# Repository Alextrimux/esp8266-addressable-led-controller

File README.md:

# esp8266-addressable-led-controller
The small hardware project of the addressable led controller on esp8266.

It is designed especially for using [WLED firmware](https://github.com/Aircoookie/WLED).

Features:
 - two-channel output for LED strip
 - reverse polarity protection
 - plug-in fuse
 - additional pins for extension

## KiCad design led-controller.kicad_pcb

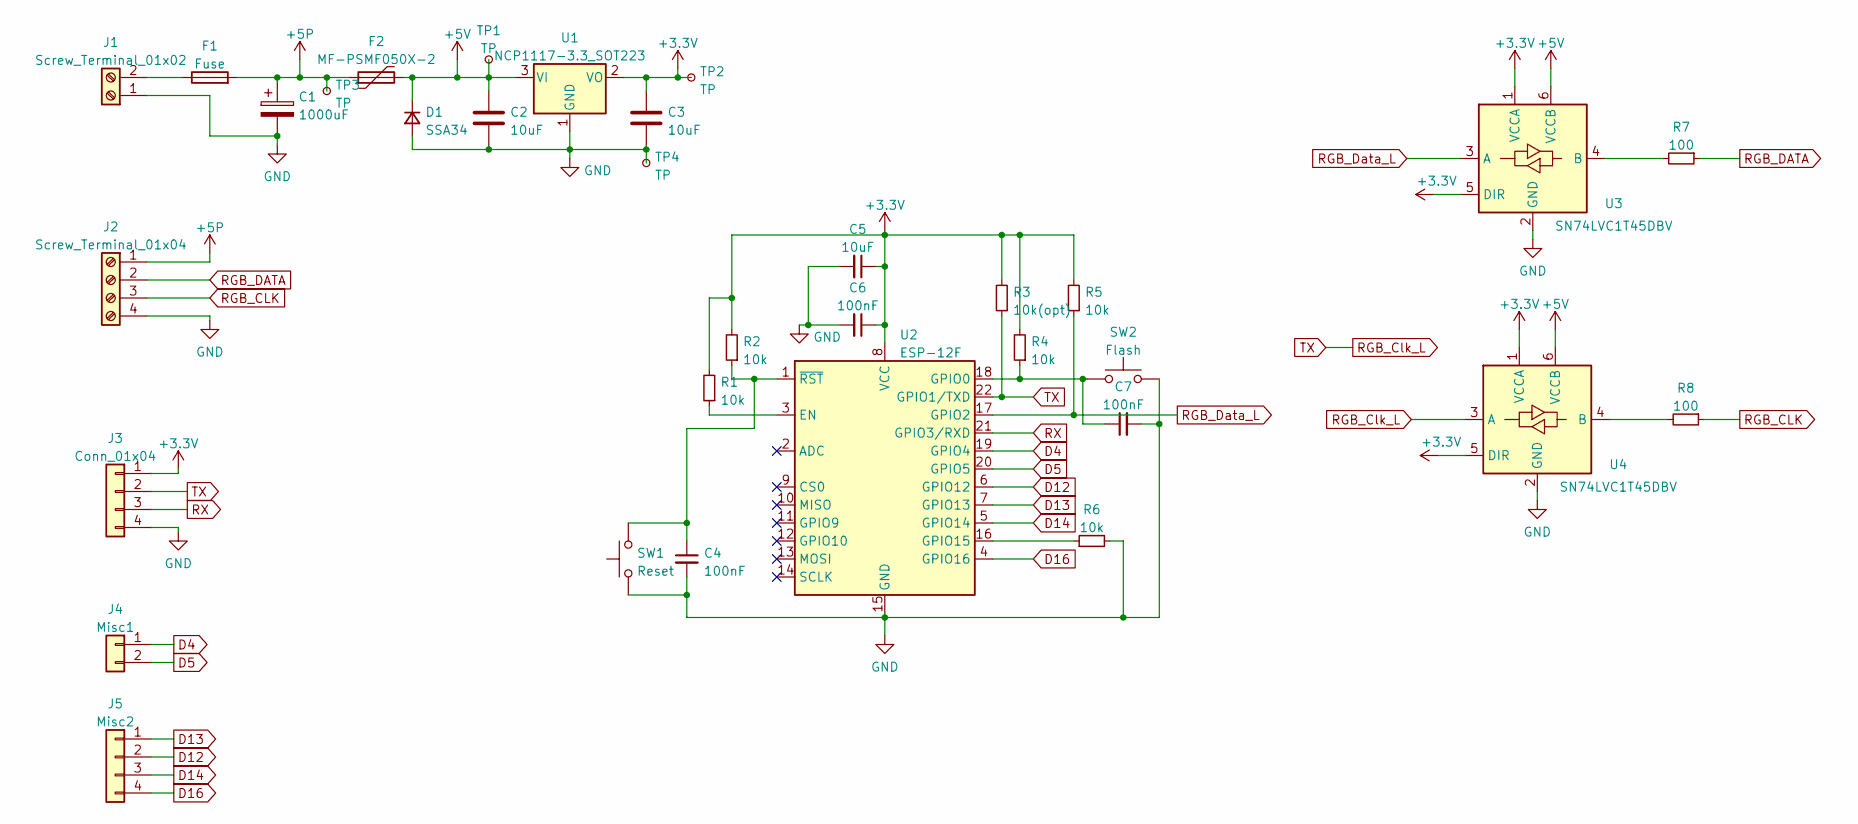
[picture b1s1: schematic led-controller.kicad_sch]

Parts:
C1: 1000uF; CP_Radial_D8.0mm_P3.50mm
C2, C3, C5: 10uF; C_0603_1608Metric_Pad1.08x0.95mm_HandSolder
C4, C6, C7: 100nF; C_0603_1608Metric_Pad1.08x0.95mm_HandSolder
D1: SSA34; D_SMA
F1: Fuse; XF-505P
F2: MF-PSMF050X-2; Fuse_0805_2012Metric_Pad1.15x1.40mm_HandSolder
J1: Screw_Terminal_01x02; TerminalBlock_bornier-2_P5.08mm
J2: Screw_Terminal_01x04; TerminalBlock_bornier-4_P5.08mm
J3: Conn_01x04; PinHeader_1x04_P2.54mm_Vertical
J4: Misc1; PinHeader_1x02_P2.54mm_Vertical
J5: Misc2; PinHeader_1x04_P2.54mm_Vertical
R1, R2, R4, R5, R6: 10k; R_0603_1608Metric_Pad0.98x0.95mm_HandSolder
R3: 10k(opt); R_0603_1608Metric_Pad0.98x0.95mm_HandSolder
R7, R8: 100; R_0603_1608Metric_Pad0.98x0.95mm_HandSolder
SW1: Reset; SW_SPST_TL3342
SW2: Flash; SW_SPST_TL3342
TP1, TP2, TP3, TP4: TP; TestPoint_Pad_D1.5mm
U1: NCP1117-3.3_SOT223; SOT-223-3_TabPin2
U2: ESP-12F; ESP-12E
U3, U4: SN74LVC1T45DBV; SOT-23-6

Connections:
+3V3: C3.1, C5.1, C6.1, J3.1, R1.2, R2.2, R3.2, R4.2, R5.2, TP2.1, U1.2 (VO), U2.8 (VCC), U3.1 (VCCA), U3.5 (DIR), U4.1 (VCCA), U4.5 (DIR)
+5P: C1.1, F1.2, F2.1, J2.1, TP3.1
+5V: C2.1, D1.1 (K), F2.2, TP1.1, U1.3 (VI), U3.6 (VCCB), U4.6 (VCCB)
D4: J4.1, U2.19 (GPIO4)
D5: J4.2, U2.20 (GPIO5)
D12: J5.2, U2.6 (GPIO12)
D13: J5.1, U2.7 (GPIO13)
D14: J5.3, U2.5 (GPIO14)
D16: J5.4, U2.4 (GPIO16)
GND: C1.2, C2.2, C3.2, C4.2, C5.2, C6.2, C7.2, D1.2 (A), J1.1, J2.4, J3.4, R6.2, SW1.1, SW2.2, TP4.1, U1.1 (GND), U2.15 (GND), U3.2 (GND), U4.2 (GND)
unnamed: C4.1, R2.1, SW1.2, U2.1 (~RST)
unnamed: C7.1, R4.1, SW2.1, U2.18 (GPIO0)
unnamed: F1.1, J1.2
unnamed: R1.1, U2.3 (EN)
unnamed: R6.1, U2.16 (GPIO15)
unnamed: R7.2, U3.4 (B)
unnamed: R8.2, U4.4 (B)
RGB_CLK: J2.3, R8.1
RGB_Clk_L: J3.2, R3.1, U2.22 (GPIO1/TXD), U4.3 (A)
RGB_DATA: J2.2, R7.1
RGB_Data_L: R5.1, U2.17 (GPIO2), U3.3 (A)
RX: J3.3, U2.21 (GPIO3/RXD)

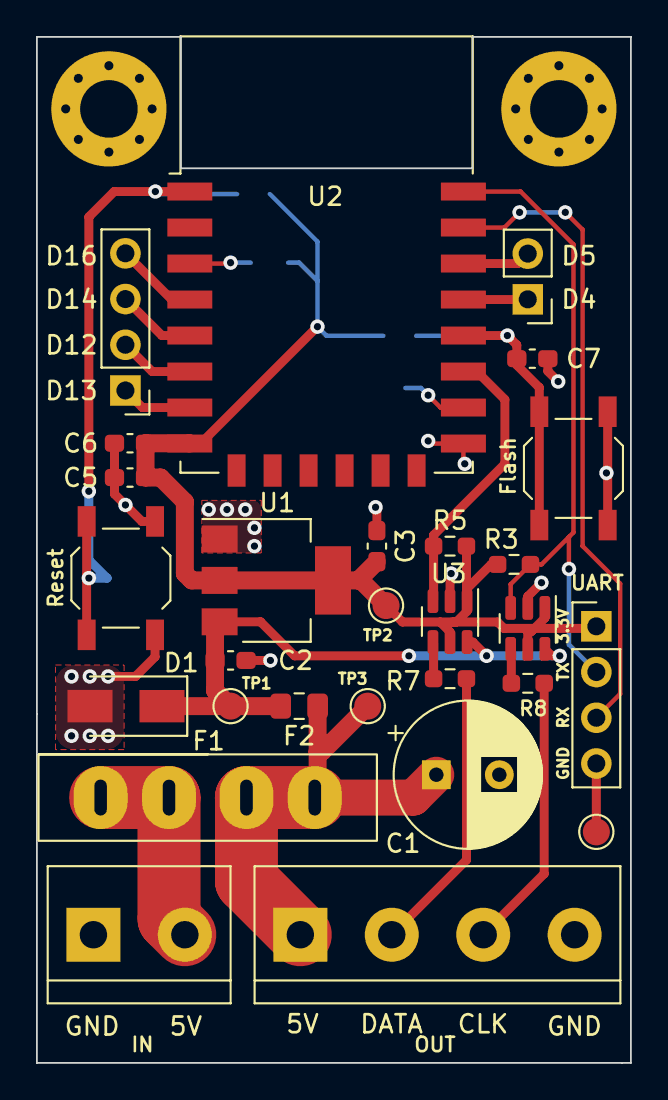
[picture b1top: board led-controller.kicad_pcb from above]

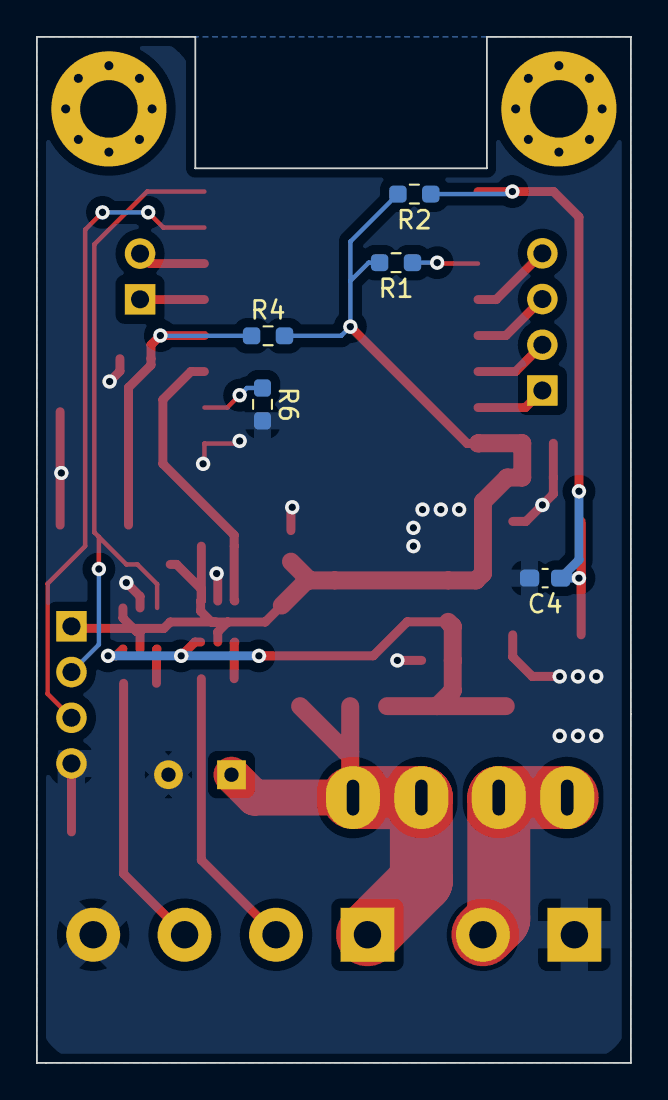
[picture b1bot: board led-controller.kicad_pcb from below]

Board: 2 copper layers, 33.0 x 57.0 mm, 33 parts (5 on the bottom side), 22 nets.

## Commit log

2023-05-30 Initialized KiCad project
2023-06-01 Designed schematic and PCB
2023-06-20 Created case for device. Added gerber files for PCB manufacturing.
2023-06-25 Upload pictures of assembled device
